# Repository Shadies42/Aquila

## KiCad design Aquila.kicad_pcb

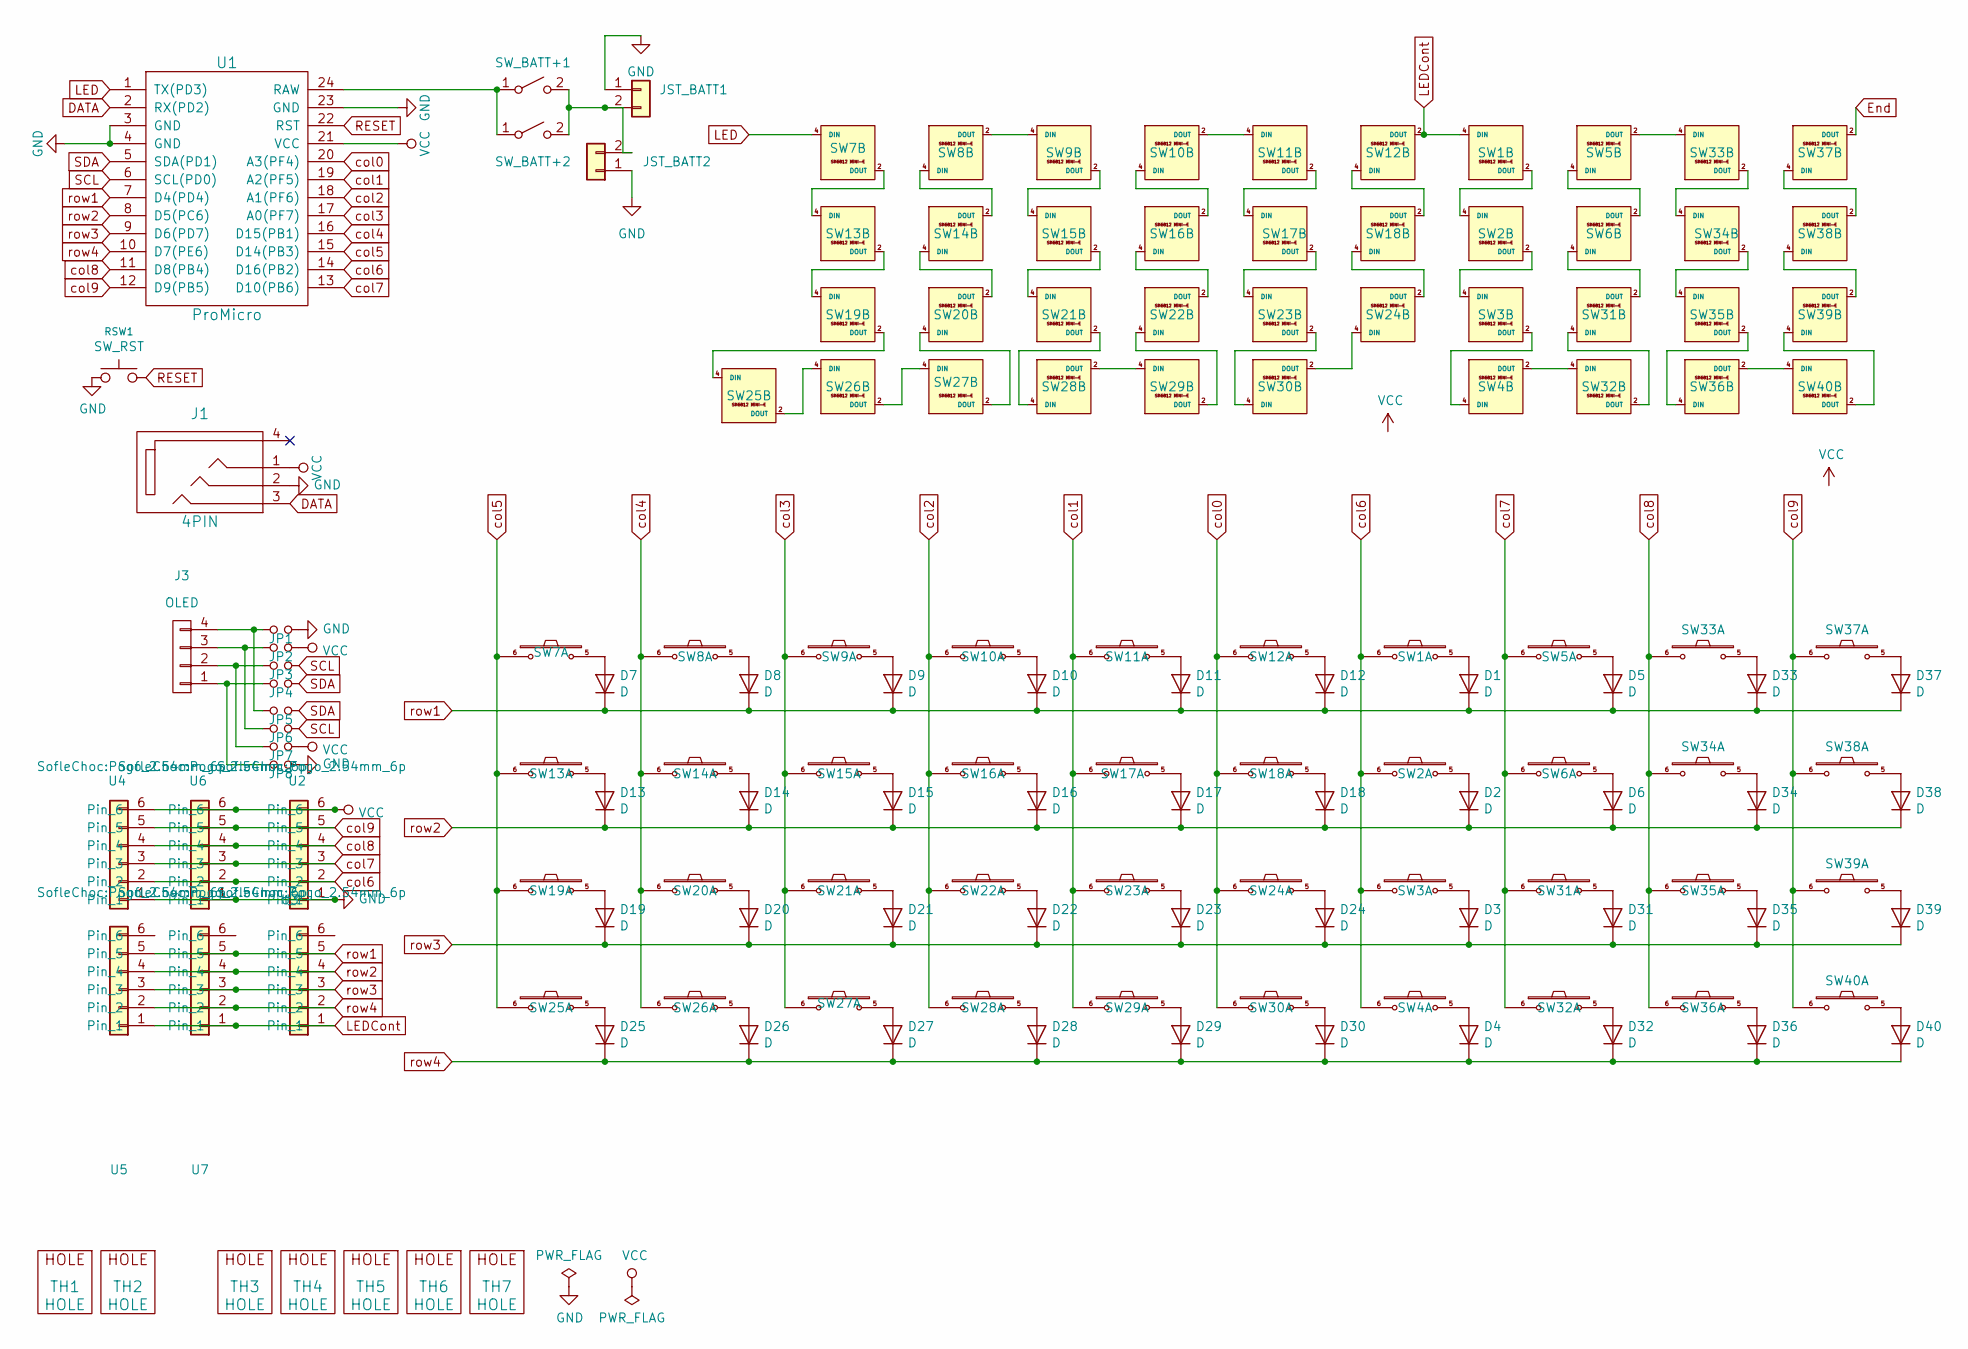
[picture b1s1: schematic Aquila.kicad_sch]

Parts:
D1, D2, D3, D4, D5, D6, D7, D8, D9, D10, D11, D12, D13, D14, D15, D16, D17, D18, D19, D20, D21, D22, D23, D24, D25, D26, D27, D28, D29, D30, D31, D32, D33, D34, D35, D36, D37, D38, D39, D40: D; crkbd-diode
J1: 4PIN; MJ-4PP-9
J3: OLED; OLED_NICEVIEW_COMBO_HDR_5Pin
JP1, JP2, JP3, JP4, JP5, JP6, JP7, JP8: Jumper_NO_Small; Jumper_small
JST_BATT1, JST_BATT2: Conn_01x02; JST_PH_S2B-PH-K_1x02_P2.00mm_DoubleSided
RSW1: SW_RST; TACT_SWITCH_TVBP06
SW1, SW2, SW3, SW4, SW5, SW6, SW7, SW8, SW9, SW10, SW11, SW12, SW13, SW14, SW15, SW16, SW17, SW18, SW19, SW20, SW21, SW22, SW23, SW24, SW25, SW26, SW27, SW28, SW29, SW30, SW31, SW32, SW33, SW34, SW35, SW36, SW37, SW38, SW39, SW40: SW_PUSH_LED; Choc_Hotswap_SK6812MiniE
SW_BATT+1, SW_BATT+2: SW_SPST; SW_SPDT_PCM12
TH1, TH2: HOLE; M2_HOLE_PCB
TH3, TH4, TH5, TH6, TH7: HOLE; HOLE_M2_TH
U1: ProMicro
U2, U3, U4, U5, U6, U7: Pogo_2.54mm_6p

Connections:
DATA: J1.3, U1.2 (RX(PD2))
End: SW37.2 (DOUT)
GND: J1.2, JP1.2, JP8.2, JST_BATT1.1, JST_BATT2.1, RSW1.1, SW1.3 (GND), SW2.3 (GND), SW3.3 (GND), SW4.3 (GND), SW5.3 (GND), SW6.3 (GND), SW7.3 (GND), SW8.3 (GND), SW9.3 (GND), SW10.3 (GND), SW11.3 (GND), SW12.3 (GND), SW13.3 (GND), SW14.3 (GND), SW15.3 (GND), SW16.3 (GND), SW17.3 (GND), SW18.3 (GND), SW19.3 (GND), SW20.3 (GND), SW21.3 (GND), SW22.3 (GND), SW23.3 (GND), SW24.3 (GND), SW25.3 (GND), SW26.3 (GND), SW27.3 (GND), SW28.3 (GND), SW29.3 (GND), SW30.3 (GND), SW31.3 (GND), SW32.3 (GND), SW33.3 (GND), SW34.3 (GND), SW35.3 (GND), SW36.3 (GND), SW37.3 (GND), SW38.3 (GND), SW39.3 (GND), SW40.3 (GND), U1.3 (GND), U1.4 (GND), U1.23 (GND), U2.1, U4.1, U6.1
LED: SW7.4 (DIN), U1.1 (TX(PD3))
LEDCont: SW1.4 (DIN), SW12.2 (DOUT), U3.1, U5.1, U7.1
unnamed: D1.2 (A), SW1.5
unnamed: D2.2 (A), SW2.5
unnamed: D3.2 (A), SW3.5
unnamed: D4.2 (A), SW4.5
unnamed: D5.2 (A), SW5.5
unnamed: D6.2 (A), SW6.5
unnamed: D7.2 (A), SW7.5
unnamed: D8.2 (A), SW8.5
unnamed: D9.2 (A), SW9.5
unnamed: D10.2 (A), SW10.5
unnamed: D11.2 (A), SW11.5
unnamed: D12.2 (A), SW12.5
unnamed: D13.2 (A), SW13.5
unnamed: D14.2 (A), SW14.5
unnamed: D15.2 (A), SW15.5
unnamed: D16.2 (A), SW16.5
unnamed: D17.2 (A), SW17.5
unnamed: D18.2 (A), SW18.5
unnamed: D19.2 (A), SW19.5
unnamed: D20.2 (A), SW20.5
unnamed: D21.2 (A), SW21.5
unnamed: D22.2 (A), SW22.5
unnamed: D23.2 (A), SW23.5
unnamed: D24.2 (A), SW24.5
unnamed: D25.2 (A), SW25.5
unnamed: D26.2 (A), SW26.5
unnamed: D27.2 (A), SW27.5
unnamed: D28.2 (A), SW28.5
unnamed: D29.2 (A), SW29.5
unnamed: D30.2 (A), SW30.5
unnamed: D31.2 (A), SW31.5
unnamed: D32.2 (A), SW32.5
unnamed: D33.2 (A), SW33.5
unnamed: D34.2 (A), SW34.5
unnamed: D35.2 (A), SW35.5
unnamed: D36.2 (A), SW36.5
unnamed: D37.2 (A), SW37.5
unnamed: D38.2 (A), SW38.5
unnamed: D39.2 (A), SW39.5
unnamed: D40.2 (A), SW40.5
unnamed: J3.1, JP4.1, JP8.1
unnamed: J3.2, JP3.1, JP7.1
unnamed: J3.3, JP2.1, JP6.1
unnamed: J3.4, JP1.1, JP5.1
unnamed: JST_BATT1.2, JST_BATT2.2, SW_BATT+1.2 (B), SW_BATT+2.2 (B)
unnamed: SW1.2 (DOUT), SW2.4 (DIN)
unnamed: SW2.2 (DOUT), SW3.4 (DIN)
unnamed: SW3.2 (DOUT), SW4.4 (DIN)
unnamed: SW5.4 (DIN), SW6.2 (DOUT)
unnamed: SW8.2 (DOUT), SW9.4 (DIN)
unnamed: SW10.4 (DIN), SW16.2 (DOUT)
unnamed: SW10.2 (DOUT), SW11.4 (DIN)
unnamed: SW11.2 (DOUT), SW17.4 (DIN)
unnamed: SW12.4 (DIN), SW18.2 (DOUT)
unnamed: SW7.2 (DOUT), SW13.4 (DIN)
unnamed: SW13.2 (DOUT), SW19.4 (DIN)
unnamed: SW14.4 (DIN), SW20.2 (DOUT)
unnamed: SW8.4 (DIN), SW14.2 (DOUT)
unnamed: SW9.2 (DOUT), SW15.4 (DIN)
unnamed: SW15.2 (DOUT), SW21.4 (DIN)
unnamed: SW16.4 (DIN), SW22.2 (DOUT)
unnamed: SW17.2 (DOUT), SW23.4 (DIN)
unnamed: SW18.4 (DIN), SW24.2 (DOUT)
unnamed: SW19.2 (DOUT), SW25.4 (DIN)
unnamed: SW20.4 (DIN), SW27.2 (DOUT)
unnamed: SW21.2 (DOUT), SW28.4 (DIN)
unnamed: SW22.4 (DIN), SW29.2 (DOUT)
unnamed: SW23.2 (DOUT), SW30.4 (DIN)
unnamed: SW24.4 (DIN), SW30.2 (DOUT)
unnamed: SW25.2 (DOUT), SW26.4 (DIN)
unnamed: SW26.2 (DOUT), SW27.4 (DIN)
unnamed: SW28.2 (DOUT), SW29.4 (DIN)
unnamed: SW31.4 (DIN), SW32.2 (DOUT)
unnamed: SW6.4 (DIN), SW31.2 (DOUT)
unnamed: SW4.2 (DOUT), SW32.4 (DIN)
unnamed: SW5.2 (DOUT), SW33.4 (DIN)
unnamed: SW33.2 (DOUT), SW34.4 (DIN)
unnamed: SW34.2 (DOUT), SW35.4 (DIN)
unnamed: SW35.2 (DOUT), SW36.4 (DIN)
unnamed: SW36.2 (DOUT), SW40.4 (DIN)
unnamed: SW37.4 (DIN), SW38.2 (DOUT)
unnamed: SW38.4 (DIN), SW39.2 (DOUT)
unnamed: SW39.4 (DIN), SW40.2 (DOUT)
unnamed: SW_BATT+1.1 (A), SW_BATT+2.1 (A), SW_BATT+2.3, U1.24 (RAW)
RESET: RSW1.2, U1.22 (RST)
SCL: JP3.2, JP6.2, U1.6 (SCL(PD0))
SDA: JP4.2, JP5.2, U1.5 (SDA(PD1))
VCC: J1.1, JP2.2, JP7.2, SW1.1 (VCC), SW2.1 (VCC), SW3.1 (VCC), SW4.1 (VCC), SW5.1 (VCC), SW6.1 (VCC), SW7.1 (VCC), SW8.1 (VCC), SW9.1 (VCC), SW10.1 (VCC), SW11.1 (VCC), SW12.1 (VCC), SW13.1 (VCC), SW14.1 (VCC), SW15.1 (VCC), SW16.1 (VCC), SW17.1 (VCC), SW18.1 (VCC), SW19.1 (VCC), SW20.1 (VCC), SW21.1 (VCC), SW22.1 (VCC), SW23.1 (VCC), SW24.1 (VCC), SW25.1 (VCC), SW26.1 (VCC), SW27.1 (VCC), SW28.1 (VCC), SW29.1 (VCC), SW30.1 (VCC), SW31.1 (VCC), SW32.1 (VCC), SW33.1 (VCC), SW34.1 (VCC), SW35.1 (VCC), SW36.1 (VCC), SW37.1 (VCC), SW38.1 (VCC), SW39.1 (VCC), SW40.1 (VCC), U1.21 (VCC), U2.6, U4.6, U6.6
col0: SW12.6, SW18.6, SW24.6, SW30.6, U1.20 (A3(PF4))
col1: SW11.6, SW17.6, SW23.6, SW29.6, U1.19 (A2(PF5))
col2: SW10.6, SW16.6, SW22.6, SW28.6, U1.18 (A1(PF6))
col3: SW9.6, SW15.6, SW21.6, SW27.6, U1.17 (A0(PF7))
col4: SW8.6, SW14.6, SW20.6, SW26.6, U1.16 (D15(PB1))
col5: SW7.6, SW13.6, SW19.6, SW25.6, U1.15 (D14(PB3))
col6: SW1.6, SW2.6, SW3.6, SW4.6, U1.14 (D16(PB2)), U2.2, U4.2, U6.2
col7: SW5.6, SW6.6, SW31.6, SW32.6, U1.13 (D10(PB6)), U2.3, U4.3, U6.3
col8: SW33.6, SW34.6, SW35.6, SW36.6, U1.11 (D8(PB4)), U2.4, U4.4, U6.4
col9: SW37.6, SW38.6, SW39.6, SW40.6, U1.12 (D9(PB5)), U2.5, U4.5, U6.5
row1: D1.1 (K), D5.1 (K), D7.1 (K), D8.1 (K), D9.1 (K), D10.1 (K), D11.1 (K), D12.1 (K), D33.1 (K), D37.1 (K), U1.7 (D4(PD4)), U3.5, U5.5, U7.5
row2: D2.1 (K), D6.1 (K), D13.1 (K), D14.1 (K), D15.1 (K), D16.1 (K), D17.1 (K), D18.1 (K), D34.1 (K), D38.1 (K), U1.8 (D5(PC6)), U3.4, U5.4, U7.4
row3: D3.1 (K), D19.1 (K), D20.1 (K), D21.1 (K), D22.1 (K), D23.1 (K), D24.1 (K), D31.1 (K), D35.1 (K), D39.1 (K), U1.9 (D6(PD7)), U3.3, U5.3, U7.3
row4: D4.1 (K), D25.1 (K), D26.1 (K), D27.1 (K), D28.1 (K), D29.1 (K), D30.1 (K), D32.1 (K), D36.1 (K), D40.1 (K), U1.10 (D7(PE6)), U3.2, U5.2, U7.2

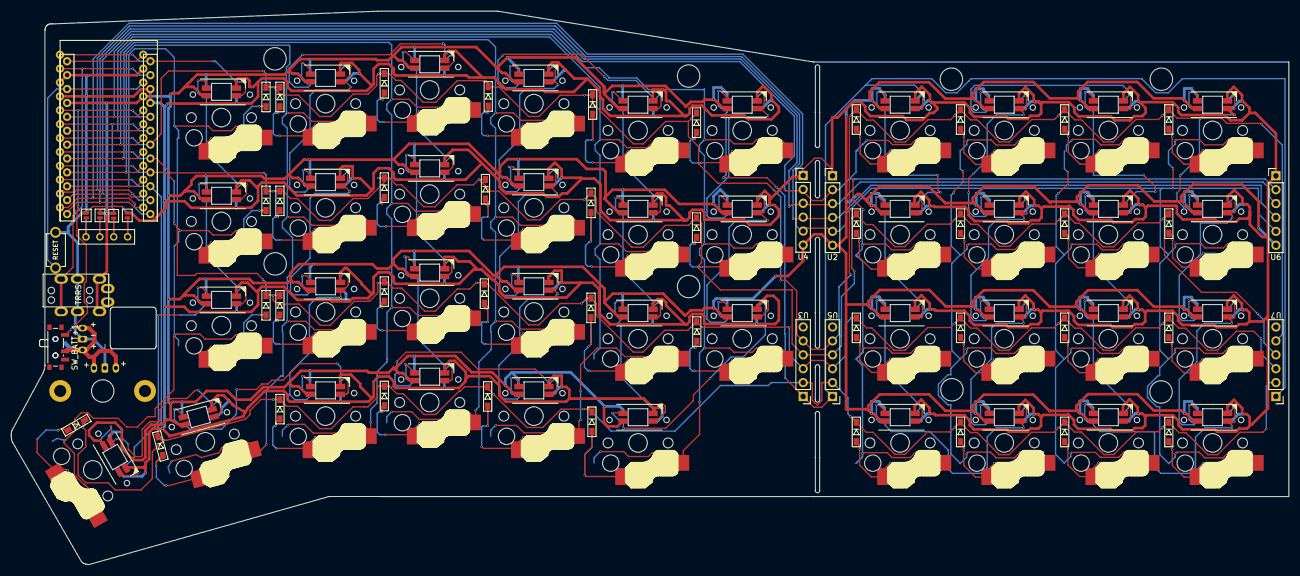
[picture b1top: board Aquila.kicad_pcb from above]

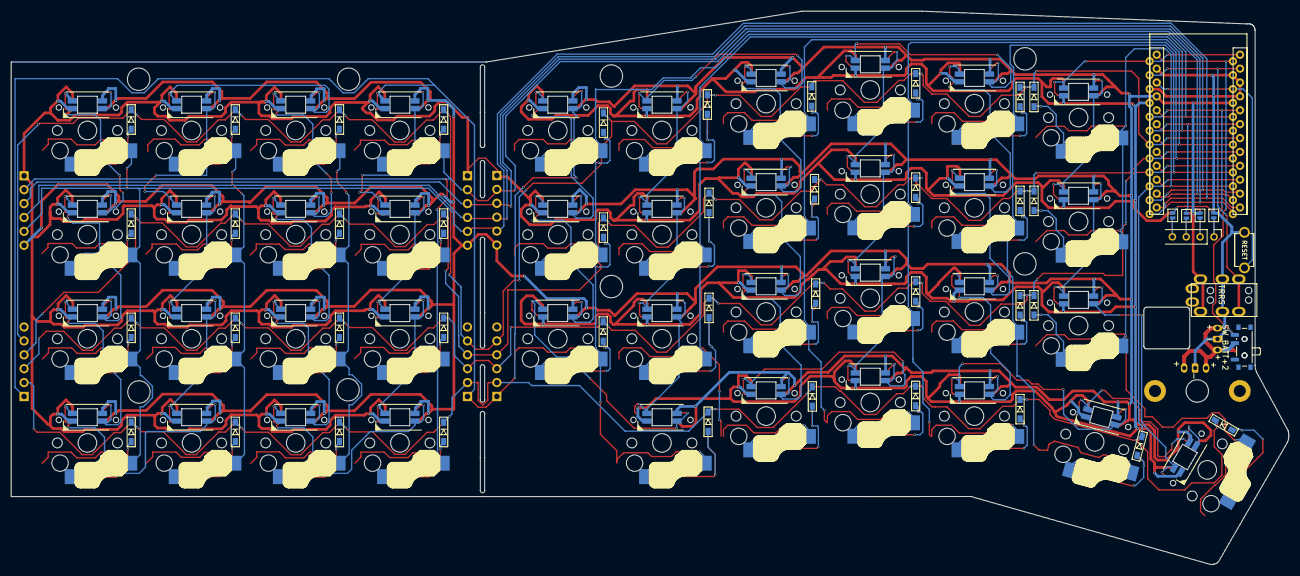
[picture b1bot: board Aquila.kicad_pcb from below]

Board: 2 copper layers, 233.7 x 101.2 mm, 113 parts (5 on the bottom side), 106 nets.

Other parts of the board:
TH3#2, TH3#3, TH3#4, TH3#5: HOLE; HOLE_M2_TH
